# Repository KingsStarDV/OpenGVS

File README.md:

# SAFETY WARNING [Read This First]
## ⚠️ Safety

OpenGVS applies a small amount of current across the mastoid (behind the ears) to stimulate the vestibular system. You are requied to read this before continuing:

**Dont Use OPENGVS or Similar Device if You::**
- Have a pacemaker, cochlear implant, or any other implanted electronic medical device
- Have epilepsy or a history of seizures
- Have any diagnosed neurological or inner-ear condition (e.g. vestibular disorders, Ménière's disease)

**Before first use:**
- Verify the output current with a multimeter — don't rely on the calculated value alone. Check if it stays within the limit before using it on skin.
- Double Check for the connections.. Any faulty connection in any of the circuit can result in flow of more current than safe.
- Test on a dummy load (for eg. a Resistor of 10k OHM)

**General:**
This is a open source Project and is not cerfitied as a medical device.. Use it with caution and at you own risk.
If you are unclear whether to use this or not, consult a doctor first..

ALSO dont use it near stairs, machineries, water or anyplace where falling can cause major injuries..

# What is a GVS ?

Simply speaking, GVS is a device which can ***HACK*** your balance. (i.e. your bodies tendency to shift either left or right to keep itself upright)

It does this by applying a **very little** current through a specific part of your head that contains the organs which sense the orientation of the body (i.e. vestibular system)

# How OPENGVS Works !

To control the balance of body we need to send **very little** current through our mastoids (i.e. the bony part right behind the ears)
This makes the current to interfere with the vestibular system and then *hack* our balance..

****BUT**** we dont want to send a lot of current through our head and fry our brain.
So the current must be limited to a **MAX OF 4mA**.

This is done through using a "current sense feedback loop". [More on this later]

I also wanted the current to be able to flow both from left to right and from right to left.
So i used a H bridge, to do so..

Thw complete thing is powered through a single 18650 cell of 3.7v

To make it wireless i decided to add a ESP32C3-Mini.

When the right firmware is uploaded in the ESP32, it starts a WiFi and theen connected to the Wifi, we meet with a webpage from where we can control wheter we want the current to flow from right to left or from left to right. (in other words i can control wheter the user moves left or right through the web page)

# The Assembly Instructions

### First of all solder the H bridge on a perf Board [or you can use a breadboard or get a PCB-- I will use a perfboard]

This is the Schematic for the H bridge.
The H bridge is pretty simple. 

The pins A, B will be connected to GPIO pins 7 & 8 of Esp32.
Pulling these pins High of Low decides the direction of the current..
The GND is connected to OFCOURSE the GND.

HOLD THE CCV pins for now..

#### Second- Solder the Current Limiting Circuit As per the Schematic.

The circuit of the bottom left of the image..

This circuits works as follow-

The transistor Q7 starts to conduct current to the pin CCV, but when a certain threshold current goes through the 220ohm resistor to Q7, the resistor creates a potential difference across it.
This potential difference is falt directly across the Base and emitter pin of the Q9.
This makes the Q9 to conduct and thus it drian all the curent to gnd..
Hence the current is limited to a certain limit through the resistor.

In this case its 3.2mA MAX.

#### Third- Add the ESP32 and battery and Volage Converters.

this is the final connection..

You can alter this last step according to your need.
the multiple mounting holes in the schematic are for only the purpose of converting 3.7v into 3.3v, nd 12v for the esp32 and H bridge to work.

# Flashing Firmware :
Flshing firmware is easiest part of this build..
Just donwload the firmware given in this repo in any compiler that you use [reccomended: Arduino IDE]
[These next steps are different for every IDE, i m using ARDUINO IDE]

then click FILES then PREFRENCES.
In "Additional Boards Manager URLs" add:

```
https://raw.githubusercontent.com/espressif/arduino-esp32/gh-pages/package_esp32_index.json
```
Then Click TOOLS, then BOARDS, then BOARD MANAGER.
Search "esp32" and install the package by Espressif Systems

NEXT, connect the esp32 c3 and in TOOLS > BAORD search and select Esp32 C3 Mini...

FInally Upload the code.
# BOM

# Bill of Materials (BOM)

## 🔌 Boards & Prototyping
| Component | Short Name | Qty | Unit Price (INR) | Subtotal (INR) | Source | Link |
|---|---|---|---|---|---|---|
| VeroBoard (6x4 Inch) | Perfboard 6x4" | 1 | 40.00 | 40.00 | Robocraze | https://robocraze.com/products/veroboard6x4?_pos=2&_sid=71be420dd&_ss=r |
| ESP32-C3 Mini Development Board - Unsoldered | ESP32-C3 Dev Board | 1 | 234.00 | 234.00 | Robocraze | https://robocraze.com/products/esp32-c3-mini-development-board-unsoldered?variant=48465411506400 |

## 🔋 Power & Charging
| Component | Short Name | Qty | Unit Price (INR) | Subtotal (INR) | Source | Link |
|---|---|---|---|---|---|---|
| TP4056 1A Li-ion Charging Module (Type-C, w/ protection) | TP4056 Li-ion Charger | 1 | 16.00 | 16.00 | Makerbazar | https://makerbazar.in/products/tp4056-1a-li-ion-lithium-battery-charging-module?variant=45459125567728 |
| 18650 SMD/SMT Battery Holder Case (Single) | 18650 Battery Holder | 1 | 39.00 | 39.00 | Makerbazar | https://makerbazar.in/products/18650-battery-holder-single-battery.js?variant=44006735 |
| Samsung SDI INR18650 Li-Ion Rechargeable Cell, 3000mAh | 18650 Li-ion Cell (3000mAh) | 1 | 249.00 | 249.00 | Makerbazar | https://makerbazar.in/products/samsung-sdi-inr18650-li-ion-rechargeable-cells?variant=48251034140912 |

## ⚡ DC-DC Converters
| Component | Short Name | Qty | Unit Price (INR) | Subtotal (INR) | Source | Link |
|---|---|---|---|---|---|---|
| DC-DC 1.8V-5V to 3.3V Booster/Buck Module | 3.3V DC-DC Converter | 1 | 52.00 | 52.00 | Robu.in | https://robu.in/product/dc-dc-1-8v-5v-to-3-3v-boost-and-buck-power-module/ |
| 3.7V to 12V Mini DC-DC Boost Step-Up Converter (5V/8V/9V/12V out) | 3.7V-12V DC-DC Boost Converter | 1 | 18.00 | 18.00 | Robu.in | https://robu.in/product/3-7v-to-12v-mini-dc-dc-boost-step-up-converter-board-module-5v-8v-9v-12v-output/ |

## 🔺 Transistors & MOSFETs
| Component | Short Name | Qty | Unit Price (INR) | Subtotal (INR) | Source | Link |
|---|---|---|---|---|---|---|
| IRLZ44N MOSFET, DIP-3 | IRLZ44N MOSFET (N-Ch) | 2 | 39.00 | 78.00 | Robu.in | https://robu.in/product/irlz44n/ |
| SPP18P06PHXKSA1 Infineon Power MOSFET, P-Ch, 60V, 18.7A, TO-220 | SPP18P06 MOSFET (P-Ch) | 2 | 180.00 | 360.00 | Robu.in | https://robu.in/product/spp18p06phxksa1-infineon-power-mosfet-p-channel/ |
| 2N3904 NPN Transistor, TO-92, onsemi | 2N3904 NPN Transistor | 2 | 18.00 | 36.00 | Robu.in | https://robu.in/product/2n3904ta-onsemi-40v-625mw-400-1ma1-0v-200ma-npn-to-92-3l-bipolar-bjt-rohs/ |
| 2N3906 PNP Transistor, TO-92, JCET | 2N3906 PNP Transistor | 2 | 5.00 | 10.00 | Robu.in | https://robu.in/product/2n3906-ta-jcet-40v-625mw-10010ma1v-200ma-pnp-to-92-bipolar-bjt-rohs/ |

## 🧩 Passive Components (Local)
| Component | Short Name | Qty | Unit Price (INR) | Subtotal (INR) | Source | Link |
|---|---|---|---|---|---|---|
| Electrode | Electrode | 2 | 15.00 | 30.00 | Local Market | N/A - local purchase |
| Resistor 220 Ohm | 220R Resistor | 1 | 10.00 | 10.00 | Local Market | N/A - local purchase |
| Resistor 10K Ohm | 10K Resistor | 5 | 10.00 | 50.00 | Local Market | N/A - local purchase |

---
**Grand Total:** ₹1,222.00
So thats all...............

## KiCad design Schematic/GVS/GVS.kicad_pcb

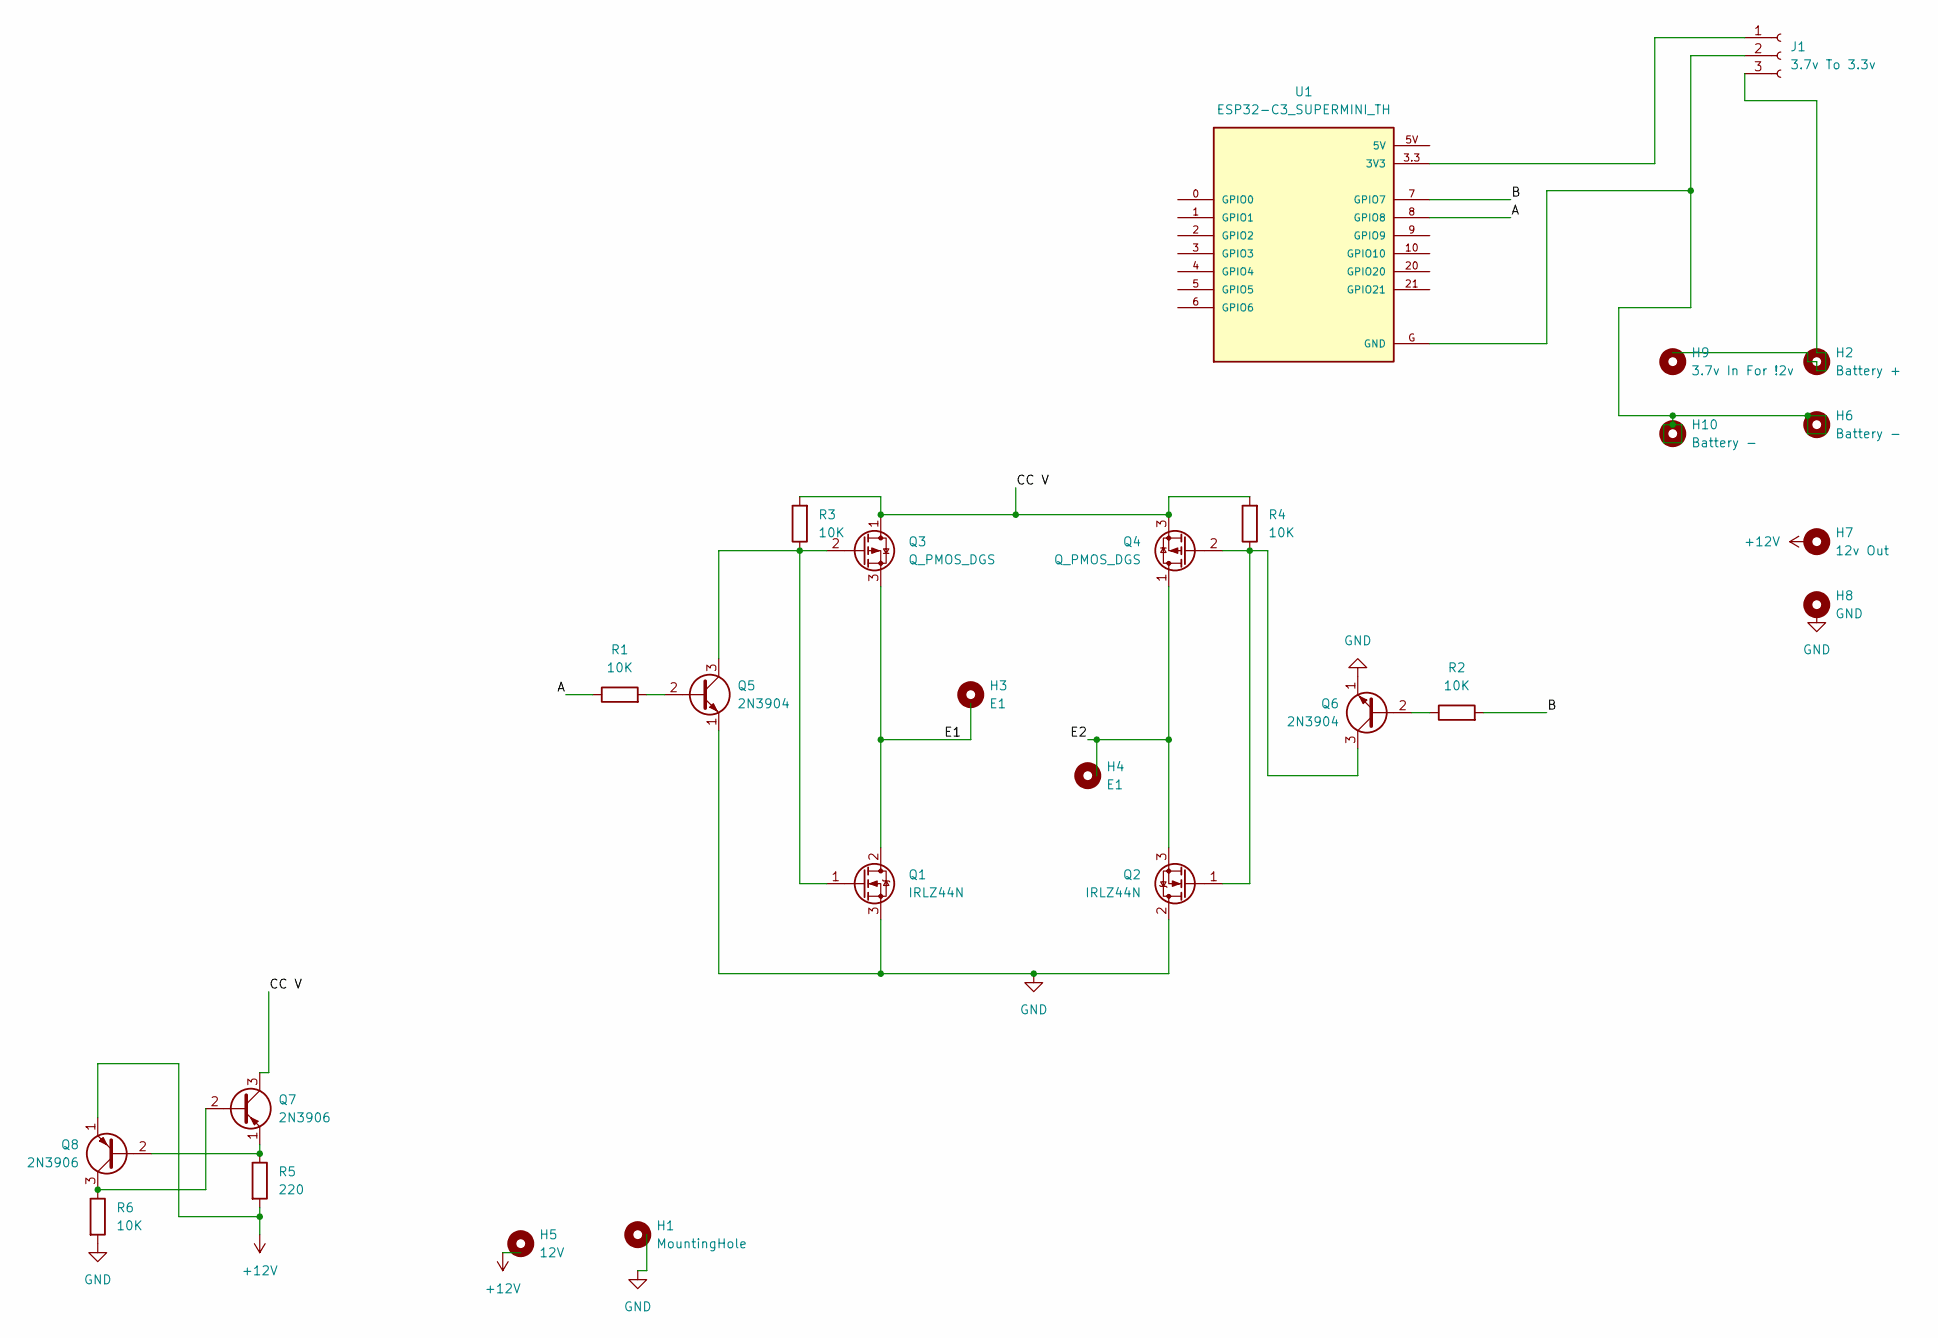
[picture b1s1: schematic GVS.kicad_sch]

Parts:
H1: MountingHole; MountingHole_2.2mm_M2_DIN965_Pad_TopBottom
H2: Battery +; MountingHole_2.2mm_M2_DIN965_Pad_TopBottom
H3, H4: E1; MountingHole_2.2mm_M2_DIN965_Pad_TopBottom
H5: 12V; MountingHole_2.2mm_M2_DIN965_Pad_TopBottom
H6, H10: Battery -; MountingHole_2.2mm_M2_DIN965_Pad_TopBottom
H7: 12v Out; MountingHole_2.2mm_M2_DIN965_Pad_TopBottom
H8: GND; MountingHole_2.2mm_M2_DIN965_Pad_TopBottom
H9: 3.7v In For !2v; MountingHole_2.2mm_M2_DIN965_Pad_TopBottom
J1: 3.7v To 3.3v; PinHeader_1x03_P2.00mm_Vertical
Q1, Q2: IRLZ44N; TO-220-3_Vertical
Q3, Q4: Q_PMOS_DGS; TO-220-3_Vertical
Q5, Q6: 2N3904; TO-92_Inline
Q7, Q8: 2N3906; TO-92_Inline
R1, R2, R3, R4, R6: 10K; R_Axial_DIN0207_L6.3mm_D2.5mm_P7.62mm_Horizontal
R5: 220; R_Axial_DIN0207_L6.3mm_D2.5mm_P7.62mm_Horizontal
U1: ESP32-C3_SUPERMINI_TH; MODULE_ESP32-C3_SUPERMINI_TH

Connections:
+12V: Q8.1 (E), R5.2
/A: R1.1, U1.8 (GPIO8)
/B: R2.2, U1.7 (GPIO7)
/CC V: Q3.1 (D), Q4.3 (S), Q7.3 (C), R3.2, R4.2
/E1: Q1.2 (D), Q3.3 (S)
/E2: Q2.3 (S), Q4.1 (D)
GND: Q1.3 (S), Q2.2 (D), Q5.1 (E), Q6.1 (E), R6.2
unnamed: J1.1, U1.3.3 (3V3)
unnamed: J1.2, U1.G (GND)
unnamed: Q1.1 (G), Q3.2 (G), Q5.3 (C), R3.1
unnamed: Q2.1 (G), Q4.2 (G), Q6.3 (C), R4.1
unnamed: Q5.2 (B), R1.2
unnamed: Q6.2 (B), R2.1
unnamed: Q7.2 (B), Q8.3 (C), R6.1
unnamed: Q7.1 (E), Q8.2 (B), R5.1

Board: 2 copper layers, 26 parts (0 on the bottom side), 15 nets, no tracks yet.
